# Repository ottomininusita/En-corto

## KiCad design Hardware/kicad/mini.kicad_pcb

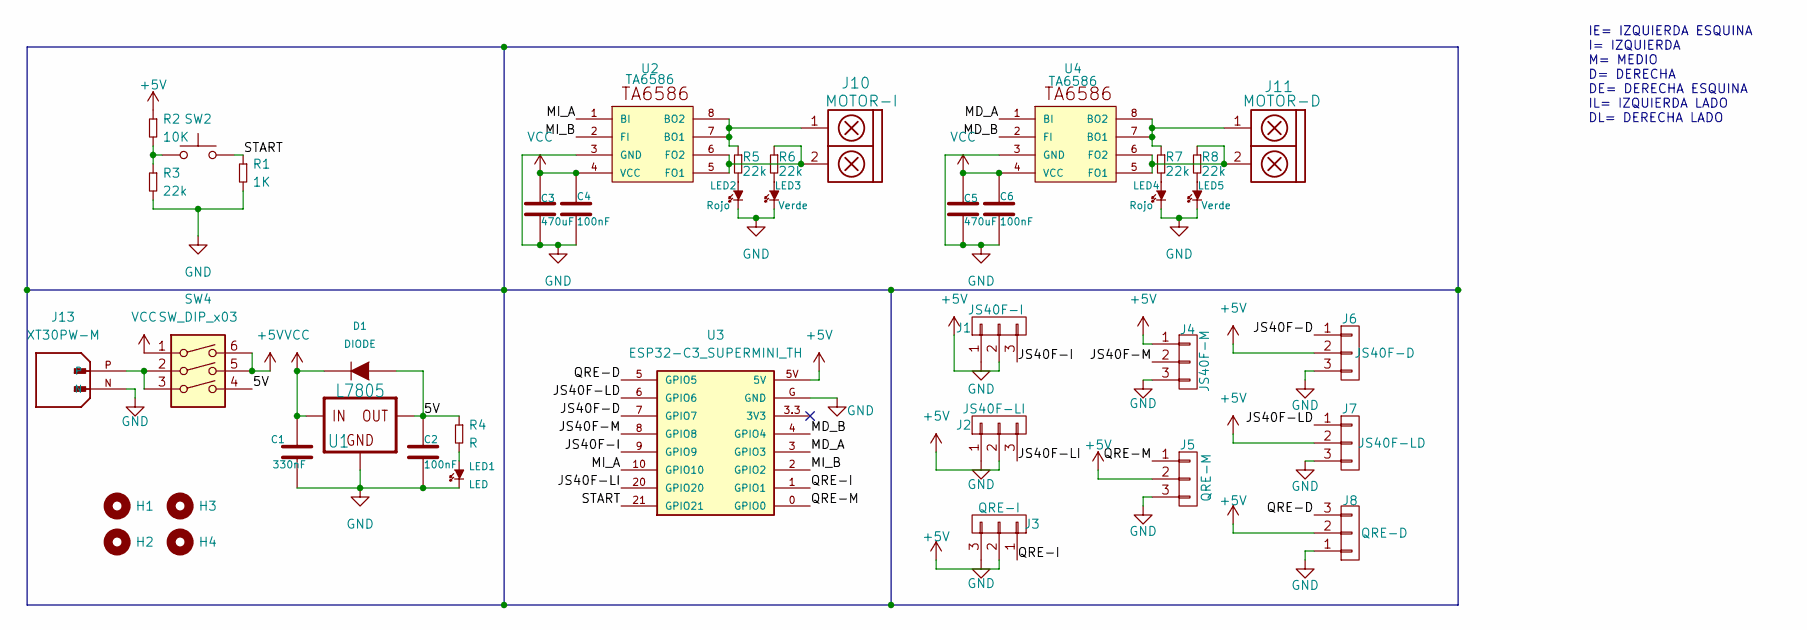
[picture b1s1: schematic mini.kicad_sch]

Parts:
C1: 330nF; C_0805
C2, C4, C6: 100nF; C_0805
C3, C5: 470uF; CP_Elec_10x10
D1: DIODE; D_1206_3216Metric_Pad1.42x1.75mm_HandSolder
H1, H2, H3, H4: Mounting_Hole; hole_3mm
J1: JS40F-I; JST_PH_B3B-PH-K_1x03_P2.00mm_Vertical
J2: JS40F-LI; JST_PH_B3B-PH-K_1x03_P2.00mm_Vertical
J3: QRE-I; JST_PH_B3B-PH-K_1x03_P2.00mm_Vertical
J4: JS40F-M; JST_PH_B3B-PH-K_1x03_P2.00mm_Vertical
J5: QRE-M; JST_PH_B3B-PH-K_1x03_P2.00mm_Vertical
J6: JS40F-D; JST_PH_B3B-PH-K_1x03_P2.00mm_Vertical
J7: JS40F-LD; JST_PH_B3B-PH-K_1x03_P2.00mm_Vertical
J8: QRE-D; JST_PH_B3B-PH-K_1x03_P2.00mm_Vertical
J10: MOTOR-I; JST_PH_B2B-PH-K_1x02_P2.00mm_Vertical
J11: MOTOR-D; JST_PH_B2B-PH-K_1x02_P2.00mm_Vertical
J13: XT30PW-M; AMASS_XT30PW-M; PARTREV 1.2
LED1: LED; LED_0805_2012Metric
LED2, LED4: Rojo; Led_0805
LED3, LED5: Verde; Led_0805
R1: 1K; R_0805
R2: 10K; R_0805
R3, R5, R6, R7, R8: 22k; R_0805
R4: R; R_0805
SW2: SW_Push; Pulsador_SMD_2_BAJO
SW4: SW_DIP_x03; SW_E-Switch_EG1271_SPDT
U1: L7805; D2PAK
U2, U4: TA6586; TA6586-FOOTPRINT
U3: ESP32-C3_SUPERMINI_TH; MODULE_ESP32-C3_SUPERMINI

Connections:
+5V: J1.2, J2.2, J3.2, J4.1, J5.2, J6.2, J7.2, J8.2, R2.1, SW4.5, SW4.6, U3.5V
/5V: C2.1, D1.1 (A), R4.1, SW4.4, U1.3 (VOUT)
/JS40F-D: J6.1, U3.7 (GPIO7)
/JS40F-I: J1.3, U3.9 (GPIO9)
/JS40F-LD: J7.1, U3.6 (GPIO6)
/JS40F-LI: J2.3, U3.20 (GPIO20)
/JS40F-M: J4.2, U3.8 (GPIO8)
/MD_A: U3.3 (GPIO3), U4.1 (BI)
/MD_B: U3.4 (GPIO4), U4.2 (FI)
/MI_A: U2.1 (BI), U3.10 (GPIO10)
/MI_B: U2.2 (FI), U3.2 (GPIO2)
/QRE-D: J8.3, U3.5 (GPIO5)
/QRE-I: J3.1, U3.1 (GPIO1)
/QRE-M: J5.1, U3.0 (GPIO0)
/START: R1.1, SW2.2, U3.21 (GPIO21)
GND: C1.2, C2.2, C3.2, C4.2, C5.2, C6.2, J1.1, J2.1, J3.3, J4.3, J5.3, J6.3, J7.3, J8.1, J13.N, LED1.2 (K), LED2.2 (K), LED3.2 (K), LED4.2 (K), LED5.2 (K), R1.2, R3.2, U1.2 (GND), U2.3 (GND), U3.G (GND), U4.3 (GND)
unnamed: J13.P, SW4.2, SW4.3
unnamed: LED1.1 (A), R4.2
unnamed: LED2.1 (A), R5.2
unnamed: LED3.1 (A), R6.2
unnamed: LED4.1 (A), R7.2
unnamed: LED5.1 (A), R8.2
unnamed: R2.2, R3.1, SW2.1
unnamed: J10.1, R5.1, U2.7 (BO1), U2.8 (BO2)
unnamed: J10.2, R6.1, U2.5 (FO1), U2.6 (FO2)
unnamed: J11.1, R7.1, U4.7 (BO1), U4.8 (BO2)
unnamed: J11.2, R8.1, U4.5 (FO1), U4.6 (FO2)
VCC: C1.1, C3.1, C4.1, C5.1, C6.1, D1.2 (K), SW4.1, U1.1 (VIN), U2.4 (VCC), U4.4 (VCC)

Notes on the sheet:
IE= IZQUIERDA ESQUINA I= IZQUIERDA M= MEDIO D= DERECHA DE= DERECHA ESQUINA IL= IZQUIERDA LADO DL= DERECHA LADO

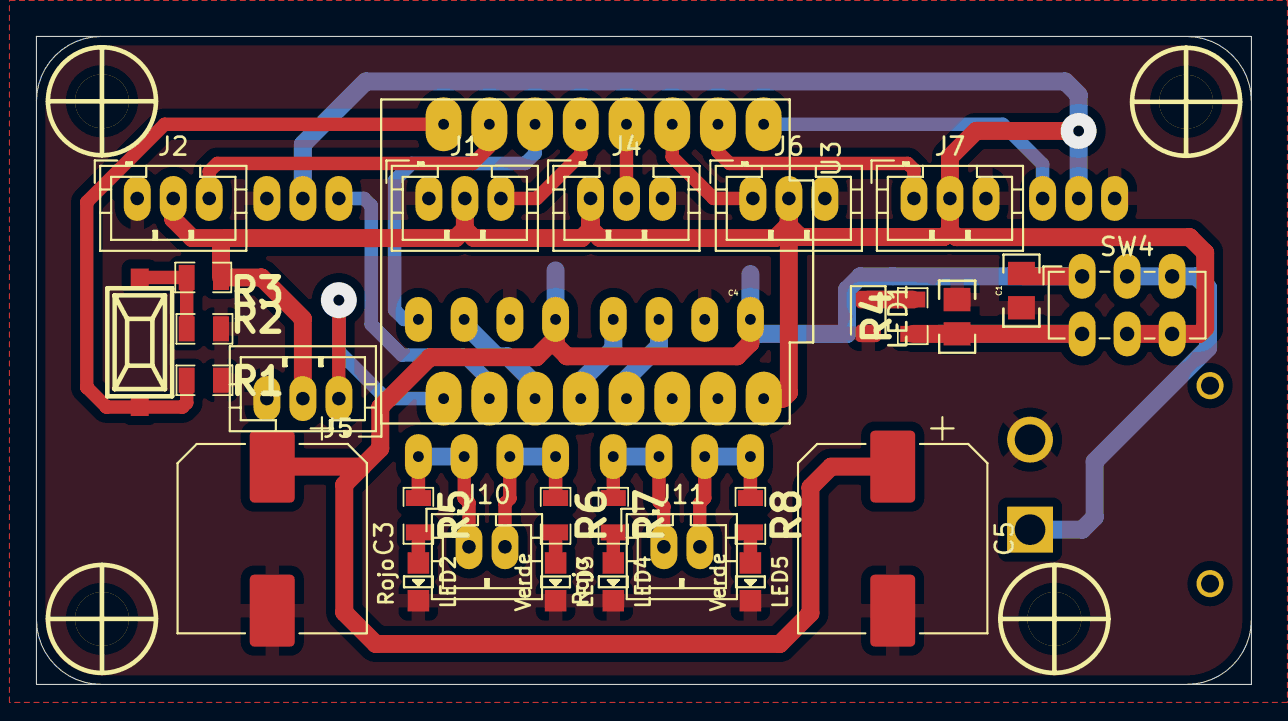
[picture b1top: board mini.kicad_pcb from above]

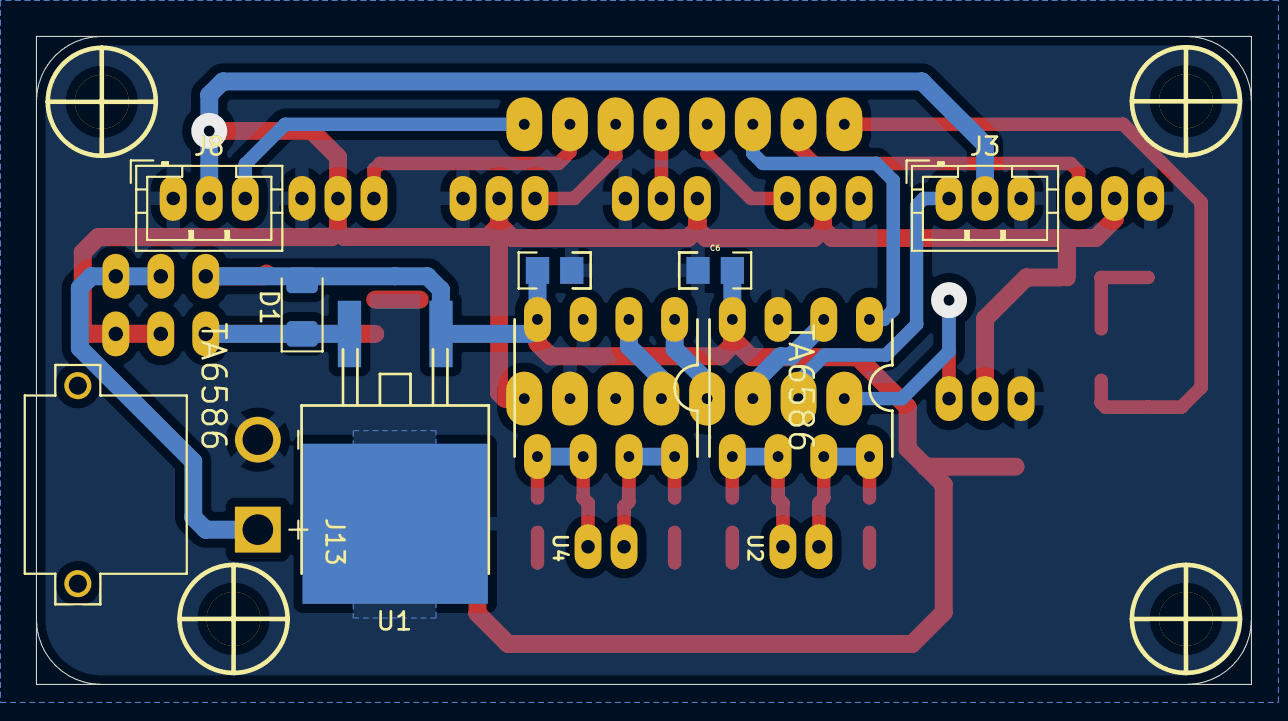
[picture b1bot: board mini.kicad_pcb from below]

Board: 2 copper layers, 67.5 x 36.0 mm, 41 parts (9 on the bottom side), 28 nets.

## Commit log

2025-05-16 primer commit
2025-05-16 actualizacion de carpetas
2025-05-16 subí el code y el 3d
2025-05-16 complementando software y hardware
2025-05-29 actu 29/05
2025-05-30 actualizacion 30/05
